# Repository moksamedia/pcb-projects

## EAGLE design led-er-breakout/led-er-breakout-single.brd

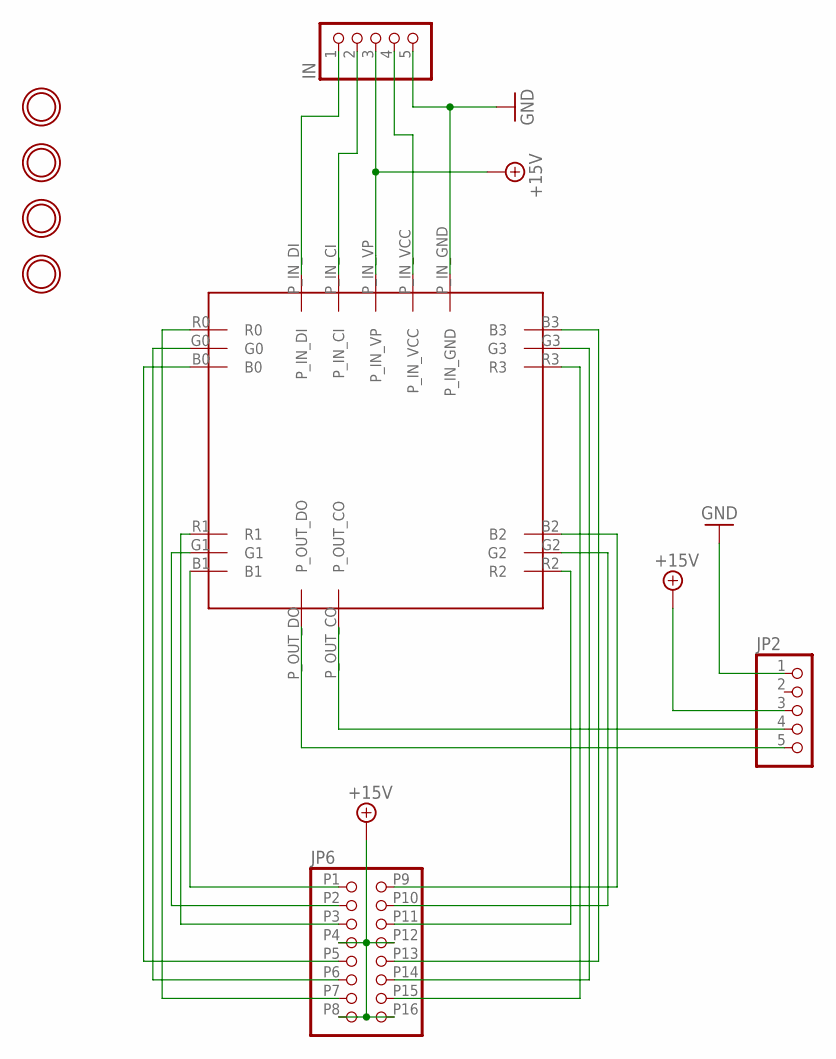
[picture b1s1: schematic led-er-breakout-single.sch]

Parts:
IN: HEADER-1X5; 1X05_OVAL
JP2: HEADER-1X5; 1X05_OVAL
JP6: HEADER-2X8; 2X08
U$1, U$2, U$3, U$4: MOUNTINGHOLE2.0; MOUNTINGHOLE_2.0_PLATED
U$6: TLC59711_BREAKOUT

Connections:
+15V: IN.3, JP2.3, JP6.P4, JP6.P8, JP6.P12, JP6.P16, U$6.P_IN_VP
GND: IN.5, JP2.1, U$6.P_IN_GND
unnamed: JP6.P3, U$6.R1
unnamed: JP6.P2, U$6.G1
unnamed: JP6.P1, U$6.B1
unnamed: JP6.P7, U$6.R0
unnamed: JP6.P6, U$6.G0
unnamed: JP6.P5, U$6.B0
unnamed: JP6.P15, U$6.R3
unnamed: JP6.P14, U$6.G3
unnamed: JP6.P13, U$6.B3
unnamed: JP6.P11, U$6.R2
unnamed: JP6.P10, U$6.G2
unnamed: JP6.P9, U$6.B2
unnamed: IN.4, U$6.P_IN_VCC
unnamed: IN.2, U$6.P_IN_CI
unnamed: IN.1, U$6.P_IN_DI
unnamed: JP2.4, U$6.P_OUT_CO
unnamed: JP2.5, U$6.P_OUT_DO

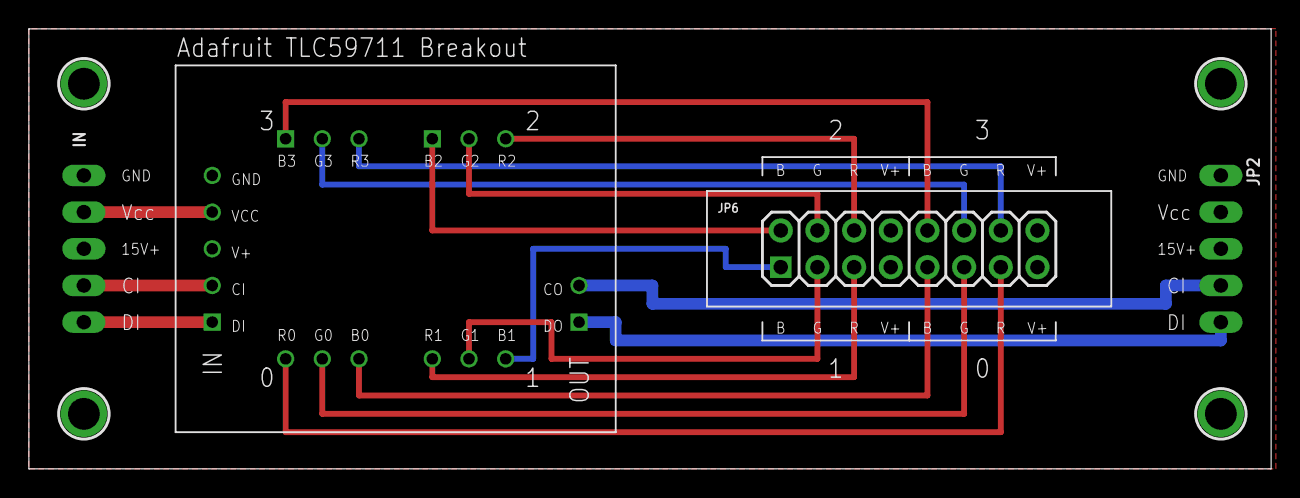
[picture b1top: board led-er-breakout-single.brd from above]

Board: 2 copper layers, 86.0 x 30.5 mm, 8 parts (0 on the bottom side), 19 nets.

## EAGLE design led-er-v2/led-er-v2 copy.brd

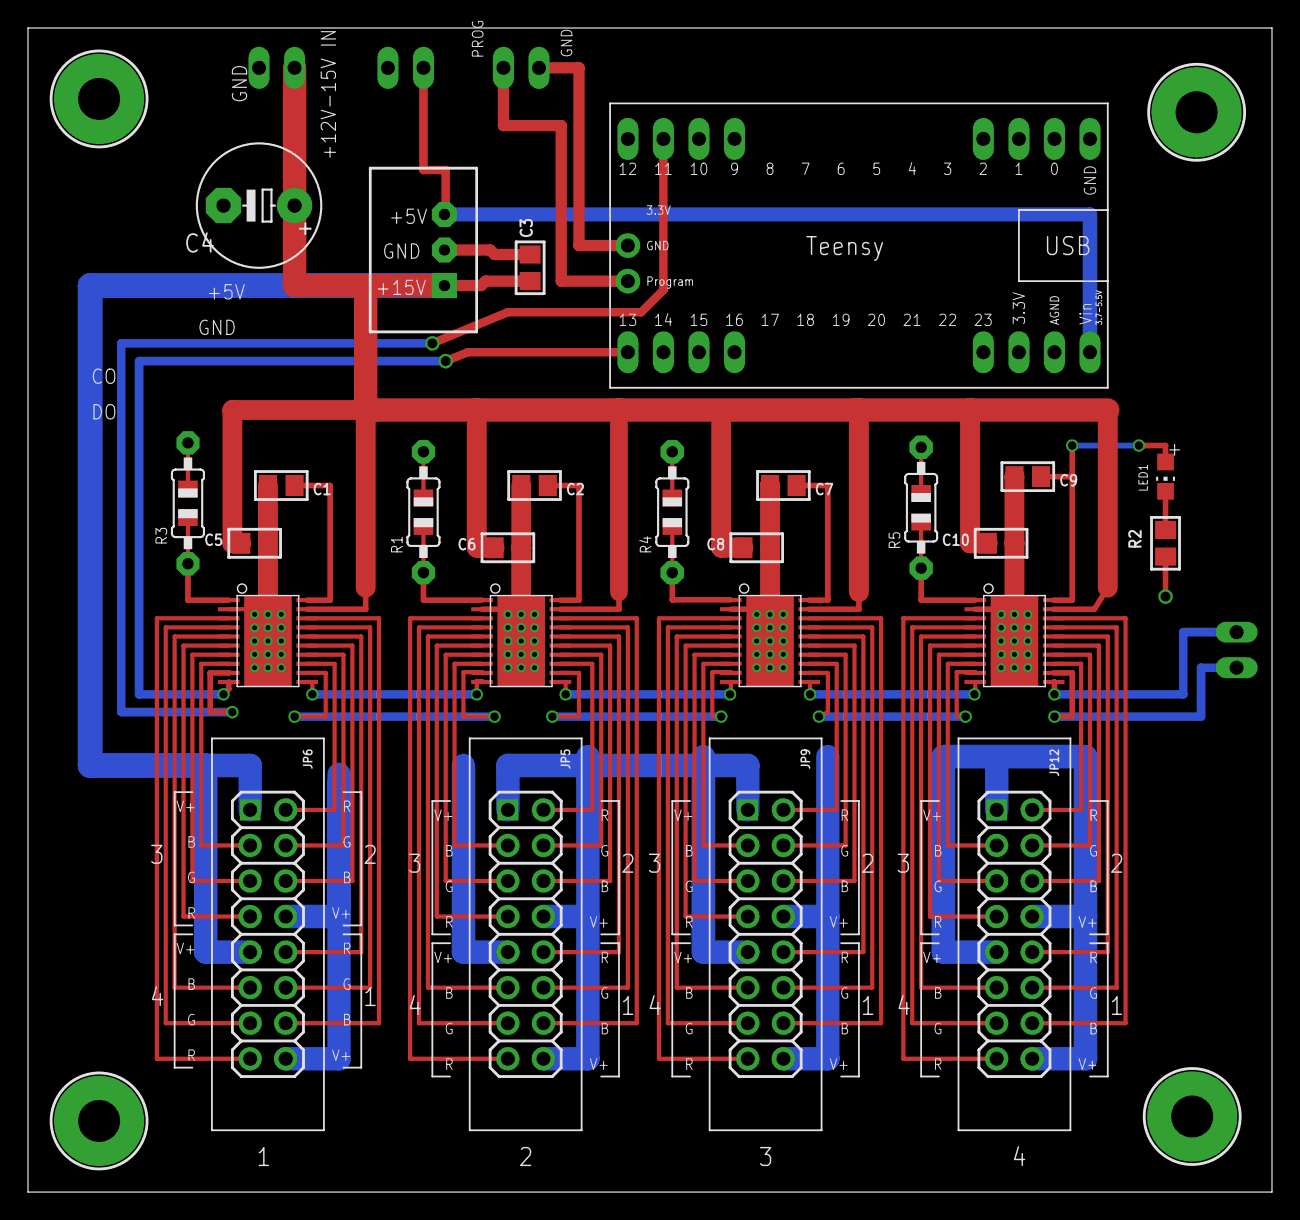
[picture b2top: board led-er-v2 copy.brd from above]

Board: 2 copper layers, 88.9 x 83.2 mm, 34 parts (0 on the bottom side), 72 nets.

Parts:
C1, C2, C3, C7, C9: 10uF/16V; 0805
C4: 220uF+; E5-8,5
C5, C6, C8, C10: 1uF/50V; 0805
IC1, IC2, IC3, IC4: TLC59711; HTSSOP20DAP
JP5, JP6, JP9, JP12: 2X08
JP_5V, JP_15VIN, JP_15VIN1: 1X02_OVAL
JP_PROG: 1X02_OVAL
LED1: Green; CHIP-LED0805
R1, R3, R4, R5: 3.3K; 0805-THM-7
R2: 470; 0805
TSR1-2450: TSR1-2450; TSR-1
U$1, U$2, U$3, U$4: MOUNTINGHOLE; MOUNTINGHOLE_3.0_PLATED
U$5: TEENSY_LEDER

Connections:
+15V: C3.1, C4.+, C5.1, C6.1, C8.1, C10.1, IC1.19, IC2.19, IC3.19, IC4.19, JP5.P1, JP5.P5, JP5.P12, JP5.P16, JP6.P1, JP6.P5, JP6.P12, JP6.P16, JP9.P1, JP9.P5, JP9.P12, JP9.P16, JP12.P1, JP12.P5, JP12.P12, JP12.P16, JP_15VIN.2, TSR1-2450.1
GND: C1.2, C2.2, C3.2, C4.-, C5.2, C6.2, C7.2, C8.2, C9.2, C10.2, IC1.2, IC1.EXP, IC2.2, IC2.EXP, IC3.2, IC3.EXP, IC4.2, IC4.EXP, JP_5V.1, JP_15VIN.1, R1.2, R2.1, R3.2, R4.2, R5.2, TSR1-2450.2, U$5.GND
JP1: JP_5V.2, TSR1-2450.3, U$5.VIN
unnamed: LED1.C, R2.2
unnamed: IC1.1, R3.1
unnamed: IC1.3, JP6.P8
unnamed: IC1.4, JP6.P7
unnamed: IC1.5, JP6.P6
unnamed: IC1.6, JP6.P4
unnamed: IC1.7, JP6.P3
unnamed: IC1.8, JP6.P2
unnamed: IC1.13, JP6.P9
unnamed: IC1.14, JP6.P10
unnamed: IC1.15, JP6.P11
unnamed: IC1.16, JP6.P13
unnamed: IC1.17, JP6.P14
unnamed: IC1.18, JP6.P15
unnamed: IC2.1, R1.1
unnamed: IC2.3, JP5.P8
unnamed: IC2.4, JP5.P7
unnamed: IC2.5, JP5.P6
unnamed: IC2.6, JP5.P4
unnamed: IC2.7, JP5.P3
unnamed: IC2.8, JP5.P2
unnamed: IC2.13, JP5.P9
unnamed: IC2.14, JP5.P10
unnamed: IC2.15, JP5.P11
unnamed: IC2.16, JP5.P13
unnamed: IC2.17, JP5.P14
unnamed: IC2.18, JP5.P15
unnamed: IC3.1, R4.1
unnamed: IC3.3, JP9.P8
unnamed: IC3.4, JP9.P7
unnamed: IC3.5, JP9.P6
unnamed: IC3.6, JP9.P4
unnamed: IC3.7, JP9.P3
unnamed: IC3.8, JP9.P2
unnamed: IC3.13, JP9.P9
unnamed: IC3.14, JP9.P10
unnamed: IC3.15, JP9.P11
unnamed: IC3.16, JP9.P13
unnamed: IC3.17, JP9.P14
unnamed: IC3.18, JP9.P15
unnamed: IC4.1, R5.1
unnamed: IC4.3, JP12.P8
unnamed: IC4.4, JP12.P7
unnamed: IC4.5, JP12.P6
unnamed: IC4.6, JP12.P4
unnamed: IC4.7, JP12.P3
unnamed: IC4.8, JP12.P2
unnamed: IC4.13, JP12.P9
unnamed: IC4.14, JP12.P10
unnamed: IC4.15, JP12.P11
unnamed: IC4.16, JP12.P13
unnamed: IC4.17, JP12.P14
unnamed: IC4.18, JP12.P15
unnamed: JP_PROG.1, U$5.GND2
unnamed: JP_PROG.2, U$5.PROG
unnamed: C1.1, IC1.20
unnamed: C7.1, IC3.20
unnamed: C2.1, IC2.20
unnamed: IC4.11, JP_15VIN1.1
unnamed: IC4.12, JP_15VIN1.2
SCKI: IC1.10, U$5.13
SCKO1: IC1.11, IC2.10
SCKO2: IC2.11, IC3.10
SCKO3: IC3.11, IC4.10
SDTI: IC1.9, U$5.11
SDTO1: IC1.12, IC2.9
SDTO2: IC2.12, IC3.9
SDTO3: IC3.12, IC4.9
VCC: C9.1, IC4.20, LED1.A

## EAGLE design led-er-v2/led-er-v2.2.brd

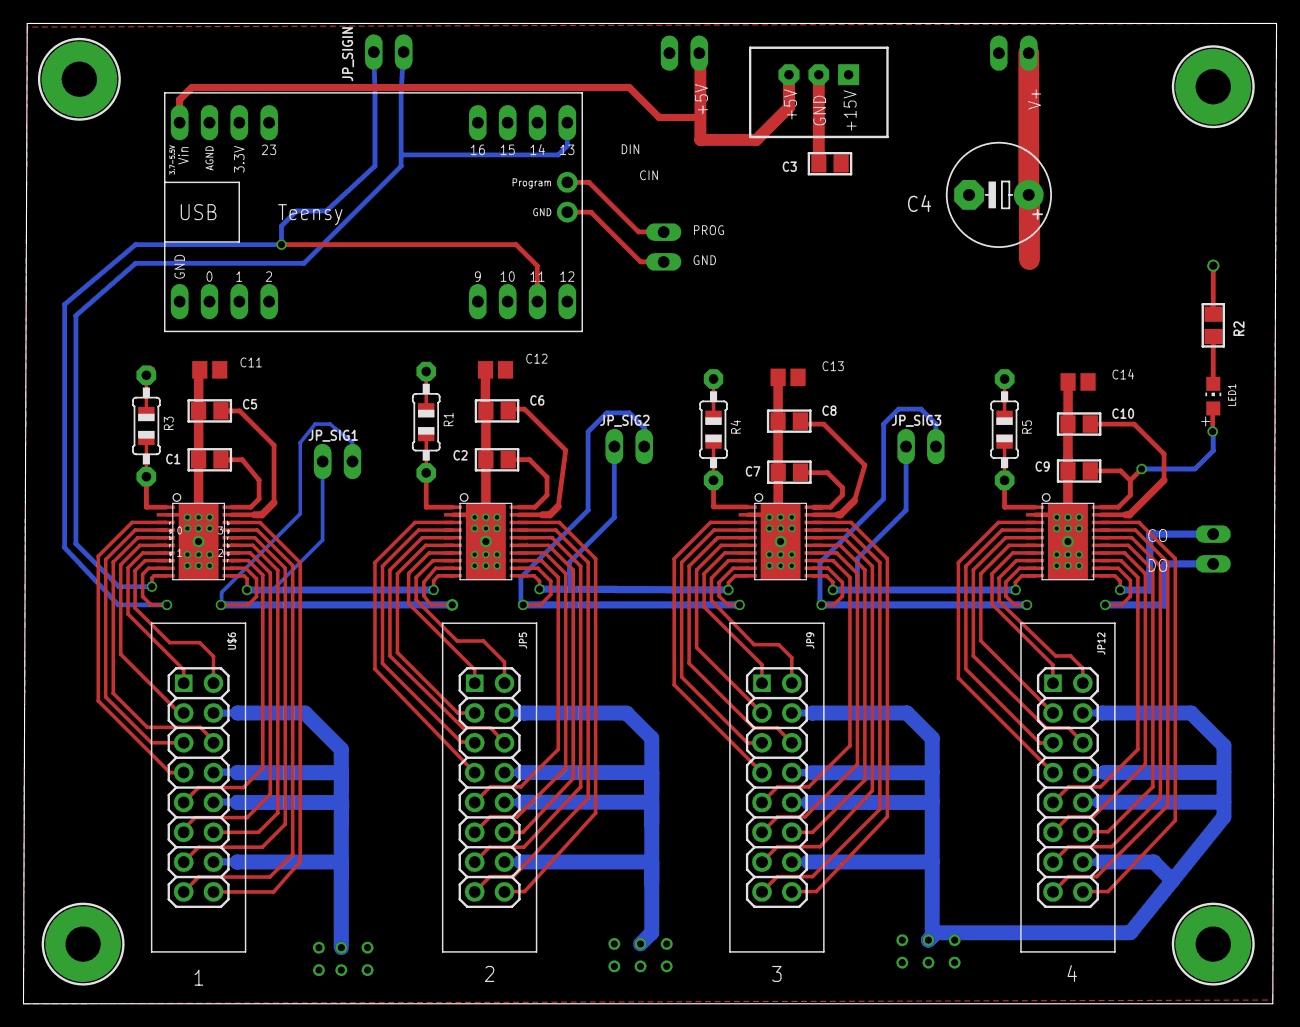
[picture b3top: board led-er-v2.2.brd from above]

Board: 2 copper layers, 106.7 x 83.5 mm, 42 parts (0 on the bottom side), 72 nets.

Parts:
C1, C2, C3, C7, C9: 10uF/16V; 0805
C4: 220uF+; E5-8,5
C5, C6, C8, C10: 1uF/50V; 0805
C11, C12, C13, C14: 10uF/25V; C0805
IC1, IC2, IC3, IC4: TLC59711; HTSSOP20DAP
JP5, JP9, JP12: HEADER-2X8-RIBBON; 2X08_RIBBON
JP_5V, JP_15VIN: 1X02_OVAL
JP_PROG: 1X02_OVAL
JP_SIG1, JP_SIG2, JP_SIG3: 1X02_OVAL
JP_SIGIN: 1X02_OVAL
JP_SIGOUT: 1X02_OVAL
LED1: Green; CHIP-LED0805
R1, R3, R4, R5: 22K; 0805-THM-7
R2: 470; 0805
TSR1-2450: TSR1-2450; TSR-1
U$1, U$2, U$3, U$4: MOUNTINGHOLE; MOUNTINGHOLE_3.0_PLATED
U$5: TEENSY_LEDER
U$6: HEADER-2X8-RIBBON; 2X08_RIBBON

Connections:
+15V: C3.1, C4.+, C5.1, C6.1, C8.1, C10.1, C11.2, C12.2, C13.2, C14.2, IC1.19, IC2.19, IC3.19, IC4.19, JP5.P3, JP5.P7, JP5.P9, JP5.P13, JP9.P3, JP9.P7, JP9.P9, JP9.P13, JP12.P3, JP12.P7, JP12.P9, JP12.P13, JP_15VIN.2, TSR1-2450.1, U$6.P3, U$6.P7, U$6.P9, U$6.P13
GND: C1.2, C2.2, C3.2, C4.-, C5.2, C6.2, C7.2, C8.2, C9.2, C10.2, C11.1, C12.1, C13.1, C14.1, IC1.2, IC1.EXP, IC2.2, IC2.EXP, IC3.2, IC3.EXP, IC4.2, IC4.EXP, JP_5V.1, JP_15VIN.1, R1.2, R2.1, R3.2, R4.2, R5.2, TSR1-2450.2, U$5.GND
JP1: JP_5V.2, TSR1-2450.3, U$5.VIN
unnamed: LED1.C, R2.2
unnamed: IC1.1, R3.1
unnamed: IC1.4, U$6.P6
unnamed: IC1.3, U$6.P8
unnamed: IC1.14, U$6.P12
unnamed: IC1.13, U$6.P10
unnamed: IC2.7, JP5.P2
unnamed: IC2.6, JP5.P4
unnamed: IC2.5, JP5.P5
unnamed: IC2.4, JP5.P6
unnamed: IC1.15, U$6.P11
unnamed: IC1.16, U$6.P14
unnamed: IC1.17, U$6.P16
unnamed: IC1.18, U$6.P15
unnamed: IC2.1, R1.1
unnamed: IC3.8, JP9.P1
unnamed: IC2.13, JP5.P10
unnamed: IC3.4, JP9.P6
unnamed: IC4.7, JP12.P2
unnamed: IC3.7, JP9.P2
unnamed: IC4.6, JP12.P4
unnamed: IC3.6, JP9.P4
unnamed: IC2.14, JP5.P12
unnamed: IC2.15, JP5.P11
unnamed: IC2.16, JP5.P14
unnamed: IC2.17, JP5.P16
unnamed: IC2.18, JP5.P15
unnamed: IC3.1, R4.1
unnamed: IC3.14, JP9.P12
unnamed: IC2.8, JP5.P1
unnamed: IC3.13, JP9.P10
unnamed: IC3.15, JP9.P11
unnamed: IC3.16, JP9.P14
unnamed: IC3.17, JP9.P16
unnamed: IC3.18, JP9.P15
unnamed: IC4.1, R5.1
unnamed: IC2.3, JP5.P8
unnamed: IC4.13, JP12.P10
unnamed: IC3.5, JP9.P5
unnamed: IC1.6, U$6.P4
unnamed: IC1.5, U$6.P5
unnamed: IC1.7, U$6.P2
unnamed: IC1.8, U$6.P1
unnamed: IC4.14, JP12.P12
unnamed: IC4.15, JP12.P11
unnamed: IC4.16, JP12.P14
unnamed: IC4.17, JP12.P16
unnamed: IC4.18, JP12.P15
unnamed: JP_PROG.1, U$5.GND2
unnamed: JP_PROG.2, U$5.PROG
unnamed: C1.1, IC1.20
unnamed: C7.1, IC3.20
unnamed: C2.1, IC2.20
unnamed: IC4.11, JP_SIGOUT.1
unnamed: IC4.12, JP_SIGOUT.2
unnamed: IC3.3, JP9.P8
unnamed: IC4.3, JP12.P8
unnamed: IC4.4, JP12.P6
unnamed: IC4.5, JP12.P5
unnamed: IC4.8, JP12.P1
SCKI: IC1.10, JP_SIGIN.2, U$5.13
SCKO1: IC1.11, IC2.10, JP_SIG1.1
SCKO2: IC2.11, IC3.10, JP_SIG2.1
SCKO3: IC3.11, IC4.10, JP_SIG3.1
SDTI: IC1.9, JP_SIGIN.1, U$5.11
SDTO1: IC1.12, IC2.9, JP_SIG1.2
SDTO2: IC2.12, IC3.9, JP_SIG2.2
SDTO3: IC3.12, IC4.9, JP_SIG3.2
VCC: C9.1, IC4.20, LED1.A

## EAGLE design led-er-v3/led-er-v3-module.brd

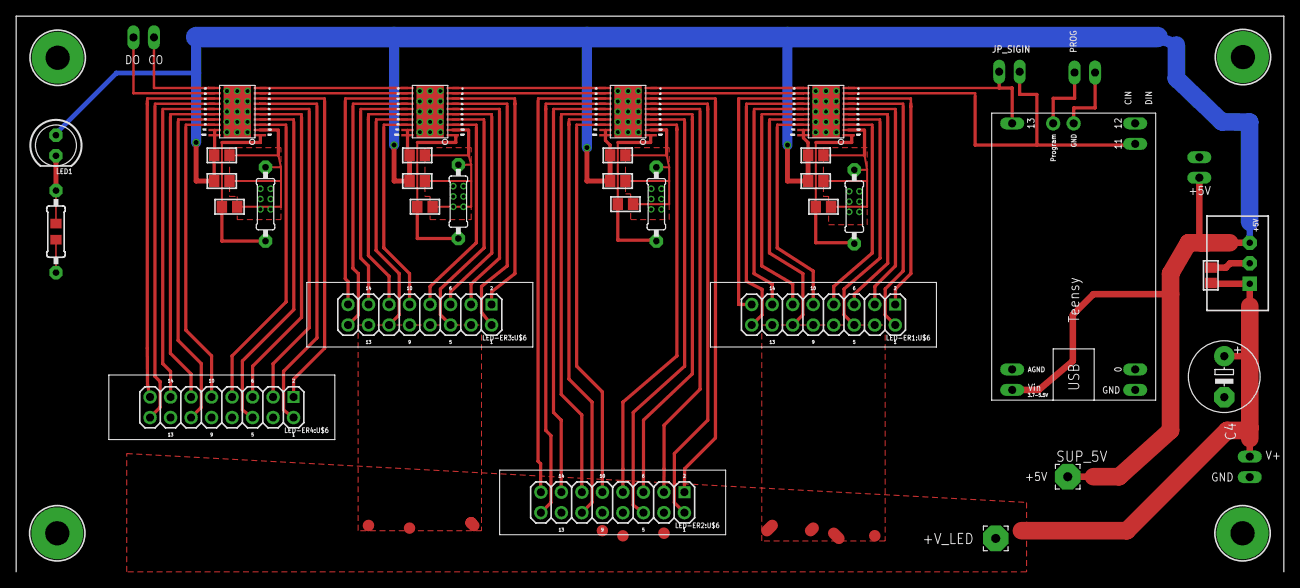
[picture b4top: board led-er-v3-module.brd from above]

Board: 2 copper layers, 157.0 x 68.8 mm, 41 parts (0 on the bottom side), 68 nets.

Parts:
+V_LED: 3,17/1,1
C3: 10uF/16V; 0805
C4: 220uF+; E5-8,5
JP_5V, JP_15VIN: 1X02_OVAL
JP_PROG: 1X02_OVAL
JP_SIGIN: 1X02_OVAL
JP_SIGOUT: 1X02_OVAL
LED1: Green; LED5MM
LED-ER1:C5, LED-ER2:C5, LED-ER3:C5, LED-ER4:C5: 1uF/50V; 0805
LED-ER1:C11, LED-ER2:C11, LED-ER3:C11, LED-ER4:C11: 10uF 25V; 0805
LED-ER1:R3, LED-ER2:R3, LED-ER3:R3, LED-ER4:R3: 22K; 0805
LED-ER1:R6, LED-ER2:R6, LED-ER3:R6, LED-ER4:R6: 0207/9
LED-ER1:TLC1, LED-ER2:TLC1, LED-ER3:TLC1, LED-ER4:TLC1: TLC59711; HTSSOP20DAP
LED-ER1:U$6, LED-ER2:U$6, LED-ER3:U$6, LED-ER4:U$6: HEADER-2X8-RIBBON; 2X08_RIBBON
R2: 470; 0805-THM
SUP_5V: 3,17/1,1
TSR1-2450: TSR1-2450; TSR-1
U$1, U$2, U$3, U$4: MOUNTINGHOLE; MOUNTINGHOLE_3.0_PLATED
U$5: TEENSY_LEDER

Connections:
1SCKI: JP_SIGIN.2, LED-ER1:TLC1.10, U$5.13
1SDTI: JP_SIGIN.1, LED-ER1:TLC1.9, U$5.11
+5V: JP_5V.2, LED1.A, LED-ER1:C5.1, LED-ER1:C11.1, LED-ER1:TLC1.19, LED-ER1:TLC1.20, LED-ER2:C5.1, LED-ER2:C11.1, LED-ER2:TLC1.19, LED-ER2:TLC1.20, LED-ER3:C5.1, LED-ER3:C11.1, LED-ER3:TLC1.19, LED-ER3:TLC1.20, LED-ER4:C5.1, LED-ER4:C11.1, LED-ER4:TLC1.19, LED-ER4:TLC1.20, SUP_5V.1, TSR1-2450.3, U$5.VIN
GND: C3.2, C4.-, JP_5V.1, JP_15VIN.1, LED-ER1:C5.2, LED-ER1:C11.2, LED-ER1:R3.2, LED-ER1:R6.2, LED-ER1:TLC1.2, LED-ER1:TLC1.EXP, LED-ER2:C5.2, LED-ER2:C11.2, LED-ER2:R3.2, LED-ER2:R6.2, LED-ER2:TLC1.2, LED-ER2:TLC1.EXP, LED-ER3:C5.2, LED-ER3:C11.2, LED-ER3:R3.2, LED-ER3:R6.2, LED-ER3:TLC1.2, LED-ER3:TLC1.EXP, LED-ER4:C5.2, LED-ER4:C11.2, LED-ER4:R3.2, LED-ER4:R6.2, LED-ER4:TLC1.2, LED-ER4:TLC1.EXP, R2.1, TSR1-2450.2, U$5.GND
LED-ER1:B0: LED-ER1:TLC1.5, LED-ER1:U$6.P6
LED-ER1:B1: LED-ER1:TLC1.8, LED-ER1:U$6.P2
LED-ER1:B2: LED-ER1:TLC1.15, LED-ER1:U$6.P14
LED-ER1:B3: LED-ER1:TLC1.18, LED-ER1:U$6.P10
LED-ER1:G0: LED-ER1:TLC1.4, LED-ER1:U$6.P5
LED-ER1:G1: LED-ER1:TLC1.7, LED-ER1:U$6.P1
LED-ER1:G2: LED-ER1:TLC1.14, LED-ER1:U$6.P15
LED-ER1:G3: LED-ER1:TLC1.17, LED-ER1:U$6.P11
LED-ER1:IREF: LED-ER1:R3.1, LED-ER1:R6.1, LED-ER1:TLC1.1
LED-ER1:R0: LED-ER1:TLC1.3, LED-ER1:U$6.P8
LED-ER1:R1: LED-ER1:TLC1.6, LED-ER1:U$6.P4
LED-ER1:R2: LED-ER1:TLC1.13, LED-ER1:U$6.P16
LED-ER1:R3: LED-ER1:TLC1.16, LED-ER1:U$6.P12
LED-ER2:B0: LED-ER2:TLC1.5, LED-ER2:U$6.P6
LED-ER2:B1: LED-ER2:TLC1.8, LED-ER2:U$6.P2
LED-ER2:B2: LED-ER2:TLC1.15, LED-ER2:U$6.P14
LED-ER2:B3: LED-ER2:TLC1.18, LED-ER2:U$6.P10
LED-ER2:G0: LED-ER2:TLC1.4, LED-ER2:U$6.P5
LED-ER2:G1: LED-ER2:TLC1.7, LED-ER2:U$6.P1
LED-ER2:G2: LED-ER2:TLC1.14, LED-ER2:U$6.P15
LED-ER2:G3: LED-ER2:TLC1.17, LED-ER2:U$6.P11
LED-ER2:IREF: LED-ER2:R3.1, LED-ER2:R6.1, LED-ER2:TLC1.1
LED-ER2:R0: LED-ER2:TLC1.3, LED-ER2:U$6.P8
LED-ER2:R1: LED-ER2:TLC1.6, LED-ER2:U$6.P4
LED-ER2:R2: LED-ER2:TLC1.13, LED-ER2:U$6.P16
LED-ER2:R3: LED-ER2:TLC1.16, LED-ER2:U$6.P12
LED-ER3:B0: LED-ER3:TLC1.5, LED-ER3:U$6.P6
LED-ER3:B1: LED-ER3:TLC1.8, LED-ER3:U$6.P2
LED-ER3:B2: LED-ER3:TLC1.15, LED-ER3:U$6.P14
LED-ER3:B3: LED-ER3:TLC1.18, LED-ER3:U$6.P10
LED-ER3:G0: LED-ER3:TLC1.4, LED-ER3:U$6.P5
LED-ER3:G1: LED-ER3:TLC1.7, LED-ER3:U$6.P1
LED-ER3:G2: LED-ER3:TLC1.14, LED-ER3:U$6.P15
LED-ER3:G3: LED-ER3:TLC1.17, LED-ER3:U$6.P11
LED-ER3:IREF: LED-ER3:R3.1, LED-ER3:R6.1, LED-ER3:TLC1.1
LED-ER3:R0: LED-ER3:TLC1.3, LED-ER3:U$6.P8
LED-ER3:R1: LED-ER3:TLC1.6, LED-ER3:U$6.P4
LED-ER3:R2: LED-ER3:TLC1.13, LED-ER3:U$6.P16
LED-ER3:R3: LED-ER3:TLC1.16, LED-ER3:U$6.P12
LED-ER4:B0: LED-ER4:TLC1.5, LED-ER4:U$6.P6
LED-ER4:B1: LED-ER4:TLC1.8, LED-ER4:U$6.P2
LED-ER4:B2: LED-ER4:TLC1.15, LED-ER4:U$6.P14
LED-ER4:B3: LED-ER4:TLC1.18, LED-ER4:U$6.P10
LED-ER4:G0: LED-ER4:TLC1.4, LED-ER4:U$6.P5
LED-ER4:G1: LED-ER4:TLC1.7, LED-ER4:U$6.P1
LED-ER4:G2: LED-ER4:TLC1.14, LED-ER4:U$6.P15
LED-ER4:G3: LED-ER4:TLC1.17, LED-ER4:U$6.P11
LED-ER4:IREF: LED-ER4:R3.1, LED-ER4:R6.1, LED-ER4:TLC1.1
LED-ER4:R0: LED-ER4:TLC1.3, LED-ER4:U$6.P8
LED-ER4:R1: LED-ER4:TLC1.6, LED-ER4:U$6.P4
LED-ER4:R2: LED-ER4:TLC1.13, LED-ER4:U$6.P16
LED-ER4:R3: LED-ER4:TLC1.16, LED-ER4:U$6.P12
unnamed: LED1.K, R2.2
unnamed: LED-ER1:TLC1.11, LED-ER2:TLC1.10
unnamed: LED-ER1:TLC1.12, LED-ER2:TLC1.9
unnamed: LED-ER2:TLC1.11, LED-ER3:TLC1.10
unnamed: LED-ER2:TLC1.12, LED-ER3:TLC1.9
unnamed: LED-ER3:TLC1.11, LED-ER4:TLC1.10
unnamed: LED-ER3:TLC1.12, LED-ER4:TLC1.9
unnamed: JP_SIGOUT.1, LED-ER4:TLC1.11
unnamed: JP_SIGOUT.2, LED-ER4:TLC1.12
unnamed: JP_PROG.1, U$5.GND2
unnamed: JP_PROG.2, U$5.PROG
VIN: +V_LED.1, C3.1, C4.+, JP_15VIN.2, LED-ER1:U$6.P3, LED-ER1:U$6.P7, LED-ER1:U$6.P9, LED-ER1:U$6.P13, LED-ER2:U$6.P3, LED-ER2:U$6.P7, LED-ER2:U$6.P9, LED-ER2:U$6.P13, LED-ER3:U$6.P3, LED-ER3:U$6.P7, LED-ER3:U$6.P9, LED-ER3:U$6.P13, LED-ER4:U$6.P3, LED-ER4:U$6.P7, LED-ER4:U$6.P9, LED-ER4:U$6.P13, TSR1-2450.1

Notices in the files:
parts and their libraries:
microbuilder: This work is placed in the public domain, and may be freely used for commercial and non-commercial work with the following conditions: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
